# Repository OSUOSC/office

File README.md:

# OSC Office Script

## Description

This code checks a serial connection to an Arduino in the Open Source Club
office, checking a photoresistor to see if the lights are on in the office and
updating a file ".office" accordingly. We serve this file to the web, so things
can check it accordingly.

1. office.py
 - This is the script that does the checking, it polls the Aruino continously
   and updates a file accordingly.
2. Boards/
 - This folder contains the physical circuit design of our CDS sheild attached
   to the arduino.
3. osccds/
 - This folder contains the Arduino sketch file.

## Installation

1. Flash the sketch "osccds" to your Arduino
2. Copy office.py to desired deployment location and create a cron job to
   ensure it runs / is running. This could also be a daemon, instead.

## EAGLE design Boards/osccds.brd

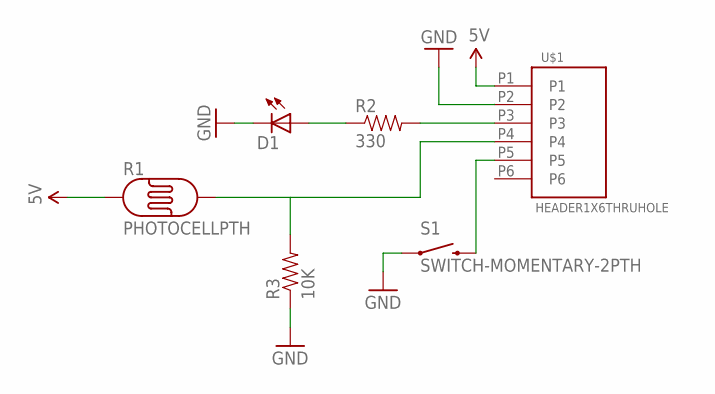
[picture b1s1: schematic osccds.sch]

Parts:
D1: LED3MM
R1: PHOTOCELLPTH; PHOTOCELL
R2: 330; AXIAL-0.3
R3: 10K; AXIAL-0.3
S1: SWITCH-MOMENTARY-2PTH; TACTILE-PTH
U$1: HEADER1X6THRUHOLE; HEADER1X6-TH

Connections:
5V: R1.1, U$1.P1
GND: D1.K (C), R3.P$1 (1), S1.1, U$1.P2
unnamed: R2.P$2 (2), U$1.P3
unnamed: D1.A, R2.P$1 (1)
unnamed: R1.2, R3.P$2 (2), U$1.P4
unnamed: S1.3 (2), U$1.P5

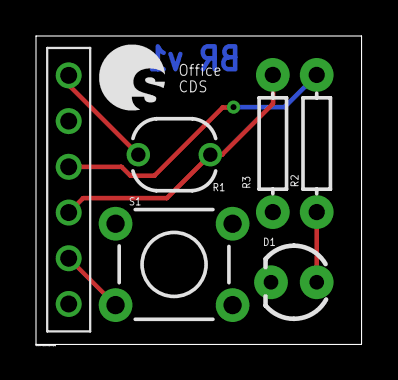
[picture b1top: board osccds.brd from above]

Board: 2 copper layers, 18.1 x 17.1 mm, 6 parts (0 on the bottom side), 6 nets.

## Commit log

2014-03-28 Initial revision
2014-03-28 Corrected code block formatting in README
2014-04-21 Begining of Time
2014-04-21 Code Documentation
2014-04-21 Added DRU and CAM jobs for OshPark processing
2014-04-24 Stallman struggled with the 115200 baud rate, 9600 works
2014-04-24 Prelim PHP Code
2014-04-24 Made PHP near equivalent to meinwalds
2014-04-24 Removed extraneous serial prints
2014-04-24 Moved from PHP to Python
2014-04-24 the old stallman checking script -> deprecated
2014-04-24 Updated README to reflect changes (arduino)
2016-03-13 Added CC0 license
    Closes #2
